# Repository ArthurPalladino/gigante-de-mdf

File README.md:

# gigante-de-mdf
O projeto gigante de MDF é um carrinho de batalha equipado com um laser como arma, capaz de detectar dano através de um LDR. Todo o sistema foi desenvolvido em C, utilizando um microcontrolador ATmega328P para controlar as funções do carrinho.

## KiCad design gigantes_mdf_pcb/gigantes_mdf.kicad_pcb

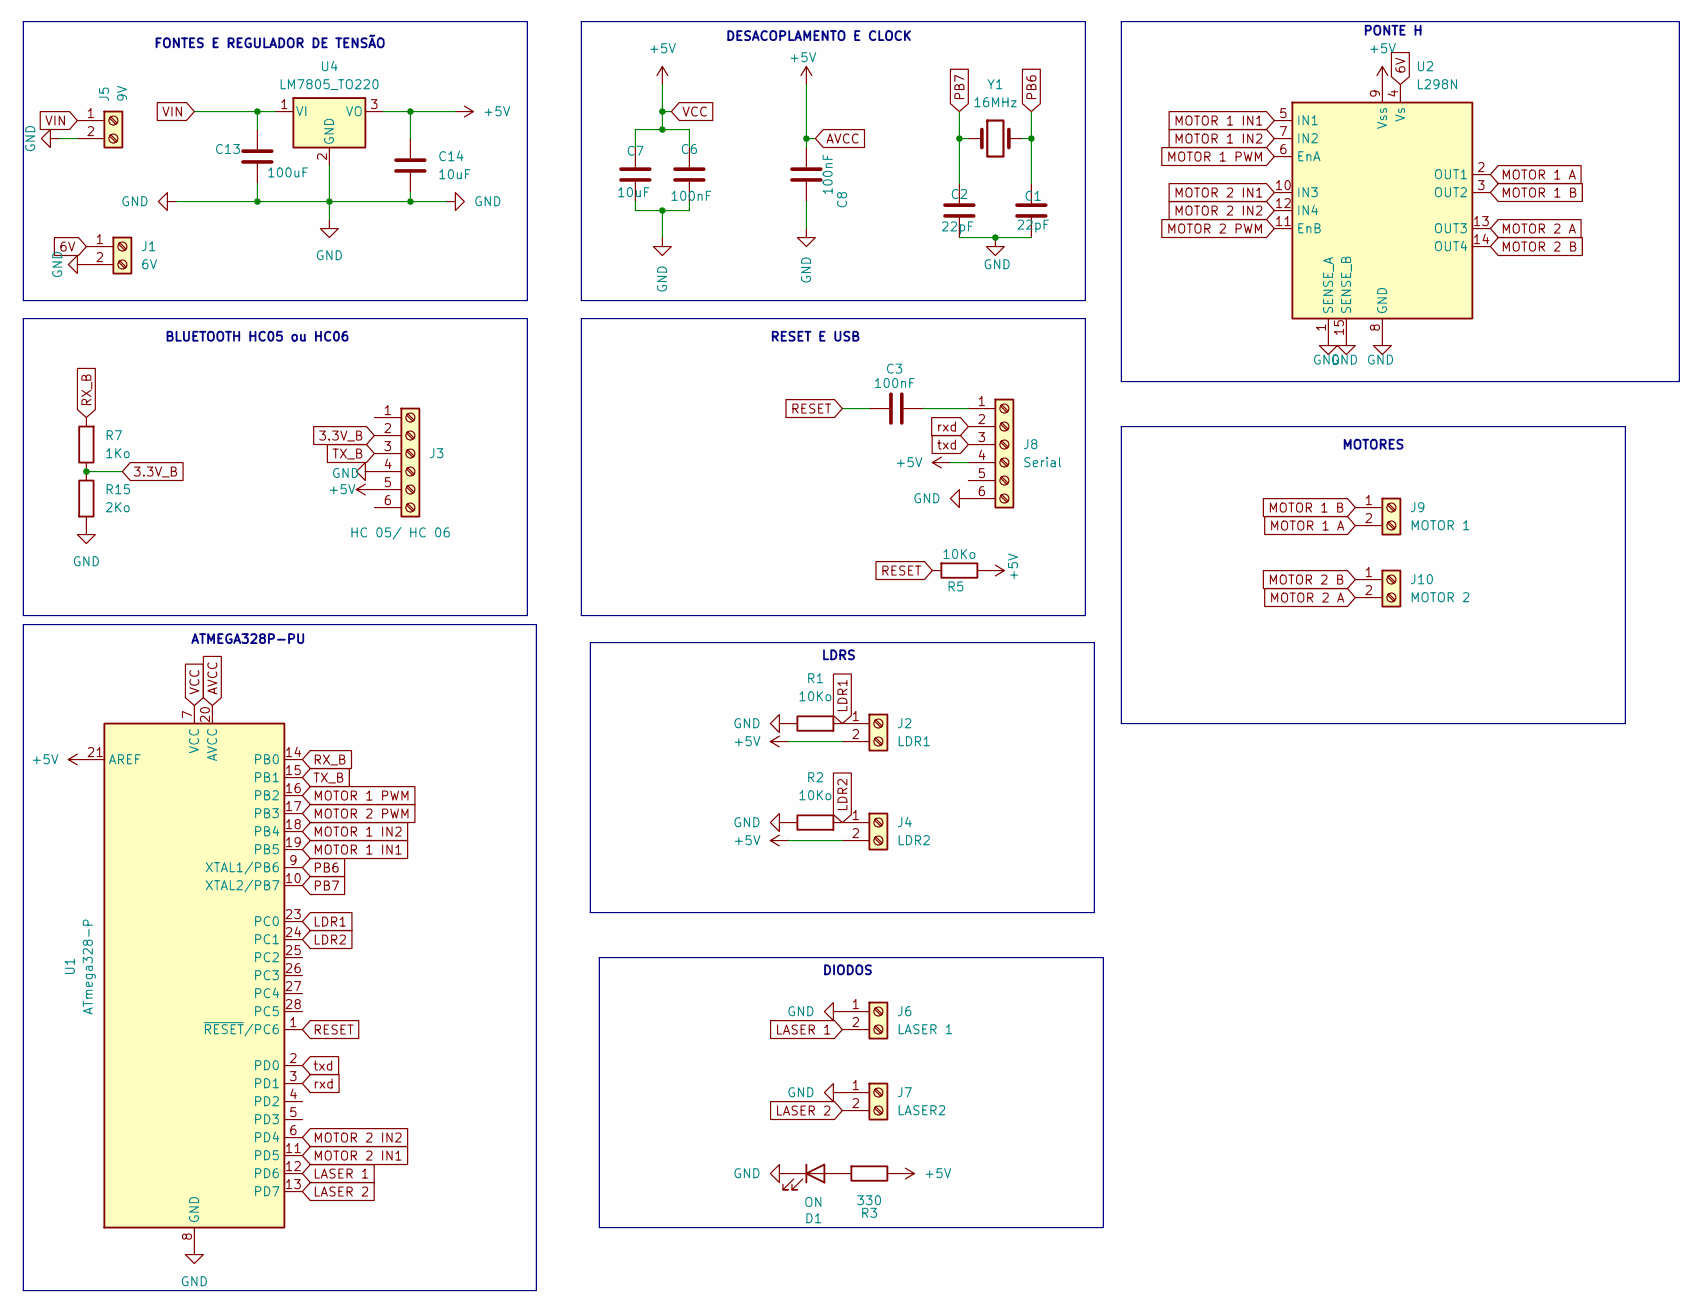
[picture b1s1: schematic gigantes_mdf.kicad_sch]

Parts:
C1, C2: 22pF; CP_Radial_Tantal_D5.5mm_P2.50mm
C3, C6, C8: 100nF; CP_Radial_Tantal_D5.5mm_P2.50mm
C7: 10uF; CP_Radial_Tantal_D5.5mm_P2.50mm
C13: 100uF; CP_Radial_D6.3mm_P2.50mm
C14: 10uF; CP_Radial_D6.3mm_P2.50mm
D1: ON; LED_D3.0mm_Horizontal_O1.27mm_Z10.0mm
J1: 6V; TerminalBlock_MaiXu_MX126-5.0-02P_1x02_P5.00mm
J2: LDR1; TerminalBlock_MaiXu_MX126-5.0-02P_1x02_P5.00mm
J3: HC 05/ HC 06; PinHeader_1x06_P2.54mm_Vertical
J4: LDR2; TerminalBlock_MaiXu_MX126-5.0-02P_1x02_P5.00mm
J5: 9V; TerminalBlock_MaiXu_MX126-5.0-02P_1x02_P5.00mm
J6: LASER 1; TerminalBlock_MaiXu_MX126-5.0-02P_1x02_P5.00mm
J7: LASER2; TerminalBlock_MaiXu_MX126-5.0-02P_1x02_P5.00mm
J8: Serial; PinHeader_1x06_P2.54mm_Vertical
J9: MOTOR 1; TerminalBlock_MaiXu_MX126-5.0-02P_1x02_P5.00mm
J10: MOTOR 2; TerminalBlock_MaiXu_MX126-5.0-02P_1x02_P5.00mm
R1, R2, R5: 10Ko; R_Axial_DIN0207_L6.3mm_D2.5mm_P10.16mm_Horizontal
R3: 330; R_Axial_DIN0207_L6.3mm_D2.5mm_P10.16mm_Horizontal
R7: 1Ko; R_Axial_DIN0207_L6.3mm_D2.5mm_P10.16mm_Horizontal
R15: 2Ko; R_Axial_DIN0207_L6.3mm_D2.5mm_P10.16mm_Horizontal
U1: ATmega328-P; DIP-28_W7.62mm
U2: L298N; TO-220-15_P2.54x5.08mm_StaggerOdd_Lead4.58mm_Vertical
U4: LM7805_TO220; TO-220-3_Vertical
Y1: 16MHz; Crystal_HC52-6mm_Vertical

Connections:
3.3V_B: J3.2, R7.1, R15.1
6V: J1.1, U2.4 (Vs)
AVCC: C6.1, C7.1, C8.2, C14.1, J2.2, J3.5, J4.2, J8.4, R3.1, R5.1, U1.7 (VCC), U1.20 (AVCC), U1.21 (AREF), U2.9 (Vss), U4.3 (VO)
GND: C1.2, C2.2, C6.2, C7.2, C8.1, C13.2, C14.2, D1.1 (K), J1.2, J3.4, J5.2, J6.1, J7.1, J8.6, R1.1, R2.1, R15.2, U1.8 (GND), U1.22 (GND), U2.1 (SENSE_A), U2.8 (GND), U2.15 (SENSE_B), U4.2 (GND)
LASER 1: J6.2, U1.12 (PD6)
LASER 2: J7.2, U1.13 (PD7)
LDR1: J2.1, R1.2, U1.23 (PC0)
LDR2: J4.1, R2.2, U1.24 (PC1)
MOTOR 1 A: J9.2, U2.2 (OUT1)
MOTOR 1 B: J9.1, U2.3 (OUT2)
MOTOR 1 IN1: U1.19 (PB5), U2.5 (IN1)
MOTOR 1 IN2: U1.18 (PB4), U2.7 (IN2)
MOTOR 1 PWM: U1.16 (PB2), U2.6 (EnA)
MOTOR 2 A: J10.2, U2.13 (OUT3)
MOTOR 2 B: J10.1, U2.14 (OUT4)
MOTOR 2 IN1: U1.11 (PD5), U2.10 (IN3)
MOTOR 2 IN2: U1.6 (PD4), U2.12 (IN4)
MOTOR 2 PWM: U1.17 (PB3), U2.11 (EnB)
unnamed: D1.2 (A), R3.2
unnamed: C3.2, J8.1
PB6: C1.1, U1.9 (XTAL1/PB6), Y1.2
PB7: C2.1, U1.10 (XTAL2/PB7), Y1.1
RESET: C3.1, R5.2, U1.1 (~RESET/PC6)
RX_B: R7.2, U1.14 (PB0)
TX_B: J3.3, U1.15 (PB1)
VIN: C13.1, J5.1, U4.1 (VI)
rxd: J8.2, U1.3 (PD1)
txd: J8.3, U1.2 (PD0)

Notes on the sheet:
PONTE H
ATMEGA328P-PU
LDRS
DIODOS
RESET E USB
MOTORES
DESACOPLAMENTO E CLOCK
BLUETOOTH HC05 ou HC06
FONTES E REGULADOR DE TENSÃO

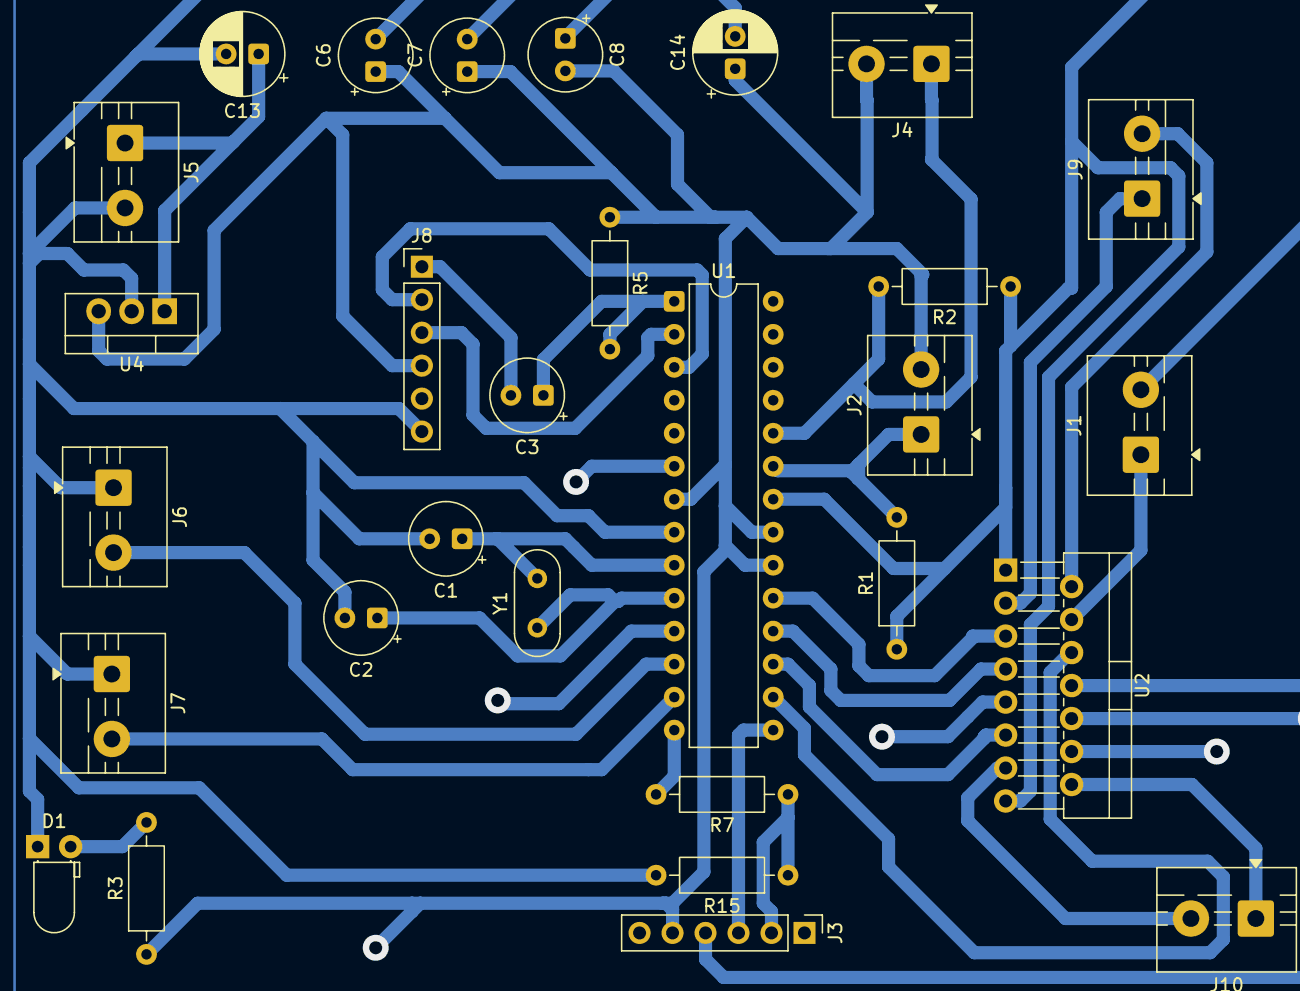
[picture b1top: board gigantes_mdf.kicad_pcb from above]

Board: 2 copper layers, 29 parts (0 on the bottom side), 28 nets.

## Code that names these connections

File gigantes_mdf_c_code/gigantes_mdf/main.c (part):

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

//RESOLVER SITUACAO DO SOFTWARE SERIAL
#define BT_RX_PIN  PB1
#define BT_RX_DDR   DDRB
#define BT_RX_PORT  PORTB
#define BT_RX_PINR  PINB

//#define BT_TX_PIN  PB0 n precisa pq so to lendo dados do serial e nao escrevendo

//PINOS
#define MOTOR1_PWM PB2   //10
#define MOTOR2_PWM PB3   //11
#define MOTOR1_IN1 PB5   //13
#define MOTOR1_IN2 PB4   //12
#define MOTOR2_IN1 PD5   //5
#define MOTOR2_IN2 PD4   //4
#define LDR        PC1   //A1
#define LASER      PD7   //7
#define RED_PIN    PC0   //A0
#define GREEN_PIN  PD6   //6


#include <avr/io.h>
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	DDRD |= (1 << GREEN_PIN);  
	
	//motor1 PWM + IN1 + IN2
	DDRB |= (1 << PB2) | (1 << PB3) | (1 << PB4) ;

	// motor2 PWM motor2 IN1 + IN2
	DDRB |= (1 << PB5);
	DDRD |= (1 << PD4) | (1 << PD5);
	
}

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
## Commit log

2025-11-25 Add complete pcb project and start new c file
2025-11-28 feat: uart serial and blutooth serial
2025-11-28 fix: update todo list
2025-11-28 feat: life led handler and laser handler
2025-11-28 feat: read ldr
2025-11-29 feat: combine all the functions and add logic to control the battle car
2025-11-29 fix: ldr threshold, 180 degrees turn over and reset life statement
